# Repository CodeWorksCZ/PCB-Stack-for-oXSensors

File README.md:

# PCB Stack for oXSensors

This PCB design focuses on creating a minimalistic and efficient PCB stack for OpenXSensor project  https://github.com/mstrens/oXs_on_RP2040 , incorporating essential features such as Li-PoL  individuall cell measurement, temperature measurement using NTC, and seamless integration with external GPS modules and on-board BMP280.

This version incorporates temperature measurement using a 10K NTC thermistor, which is not originally accounted for in the [firmware](https://github.com/mstrens/oXs_on_RP2040). Therefore, a minor code addition and code compiling is necessary.

The PCB stack can be powered by standard 5V or can handle up to 12V by configuring the solder pads. This can be useful when operating high-voltage (HV) servos at 8.4V.

**Top PCB Connectors**:

- NTC 10K Thermistor
- RPM -> to CDI
- ACS758 Current Sensor and Voltage measurement

**Bottom PCB Connectors:**

- Li-Pol Cells Measurement (up to 4S) connected to on-board ADS1115
- GPS Module - e.g. BN-220
- ACS758 Current Sensor and Voltage measurement

**PCB Stack Connectors:**

Wiring and assembly instructions can be found in https://github.com/CodeWorksCZ/PCB-Stack-for-oXSensors/wiki

The initial version lacks the capability to connect additional I2C devices.

**Wiring diagram**

Precompiled firmware with the temperature calculation  based on NTC thermistor values can be [here](/oXs%20Firmware/).

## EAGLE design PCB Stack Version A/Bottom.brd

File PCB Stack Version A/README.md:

| Bottom PCB   |   Description |
|---	|---	|
|   Bottom.brd	|   Eagle Board design of Bottom PCB	|
|   Bottom.sch	|   Eagle Schematics of Bottom PCB	|
|   Bottom.pdf	|   Schematics in PDF	|
|   Top.brd	|   Eagle Board design of Top PCB	|
|   Top.sch	|   Eagle Schematics of Top PCB	|
|   Top.pdf |   Schematics in PDF	|
|   PCB Stack oXs.f3z	|   Fusion360 Files	|

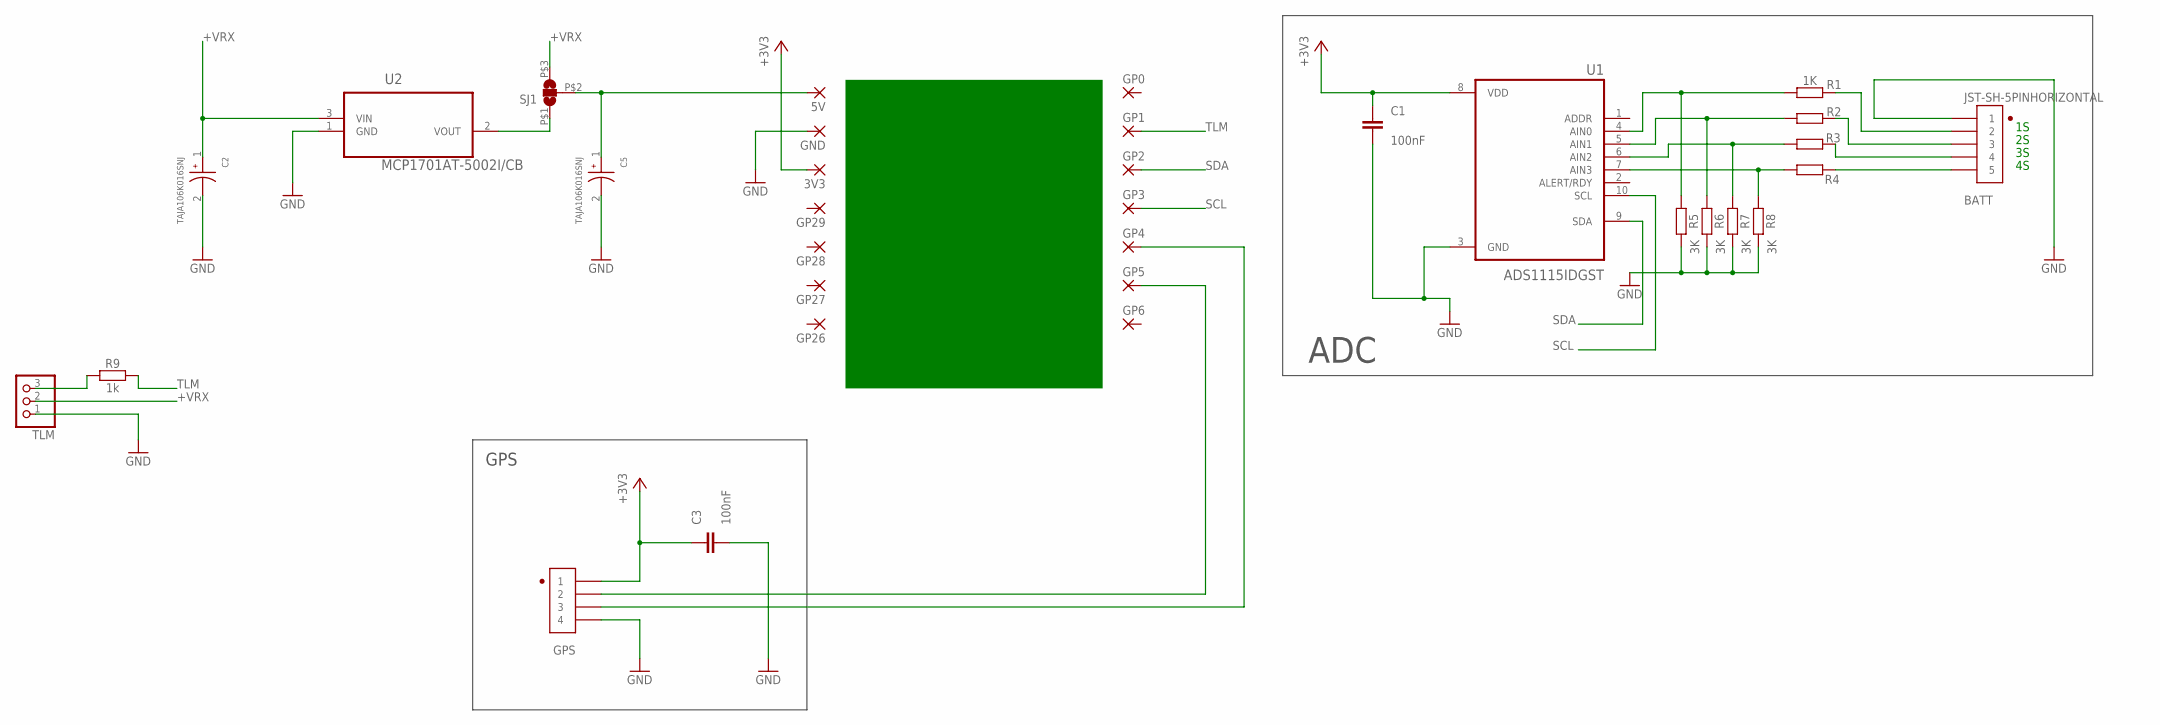
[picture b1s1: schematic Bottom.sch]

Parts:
3V3, 5V: 1,6/0,9
BATT: JST-SH-5PINHORIZONTAL; JST-SH-5PIN-1.0MM
C1, C3: 100nF; 0603
C2, C5: TAJA106K016SNJ; CAPMP3216X180N
GND: 1,6/0,9
GP0, GP1, GP2, GP3, GP4, GP5, GP6, GP26, GP27, GP28, GP29: 1,6/0,9
GPS: JST-SH-4PINJST-SH-4-HORIZONTAL; JST-SH-4PIN-1.0MM
R1: 1K; 0603
R2, R3, R4: 0603
R5, R6, R7, R8: 3K; 0603
R9: 1k; 0603
SJ1: SJ2WSJ_TINY; SJ_TINY
TLM: PINHD-1X390; 1X03-ANGLE
U1: ADS1115IDGST; SOP50P490X110-10N
U2: MCP1701AT-5002I/CB; SOT95P255X145-3N

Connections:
+3V3: 3V3.1, C1.1, C3.1, GPS.1, U1.8 (VDD)
+VRX: C2.1, SJ1.P$3 (3), TLM.2, U2.3 (VIN)
GND: BATT.1, C1.2, C2.2, C3.2, C5.2, GND.1, GPS.4, R5.2, R6.2, R7.2, R8.2, TLM.1, U1.3 (GND), U2.1 (GND)
unnamed: R1.2, R5.1, U1.4 (AIN0)
unnamed: R2.2, R6.1, U1.5 (AIN1)
unnamed: R3.2, R7.1, U1.6 (AIN2)
unnamed: R4.2, R8.1, U1.7 (AIN3)
unnamed: BATT.5, R4.1
unnamed: BATT.4, R3.1
unnamed: BATT.3, R2.1
unnamed: BATT.2, R1.1
unnamed: R9.1, TLM.3
unnamed: GP4.1, GPS.3
unnamed: GP5.1, GPS.2
unnamed: SJ1.P$1 (1), U2.2 (VOUT)
unnamed: 5V.1, C5.1, SJ1.P$2 (2)
SCL: GP3.1, U1.10 (SCL)
SDA: GP2.1, U1.9 (SDA)
TLM: GP1.1, R9.2

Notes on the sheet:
GPS
ADC

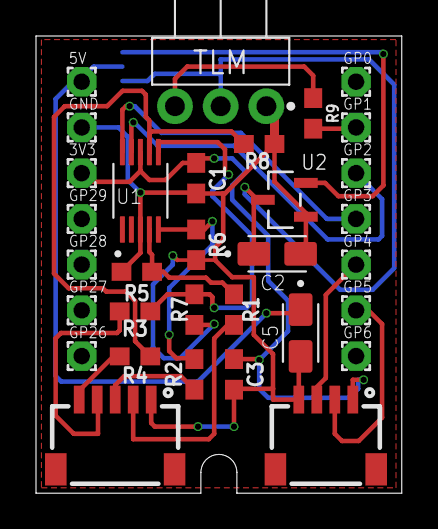
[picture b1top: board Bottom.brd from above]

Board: 2 copper layers, 20.3 x 25.4 mm, 33 parts (1 on the bottom side), 19 nets.

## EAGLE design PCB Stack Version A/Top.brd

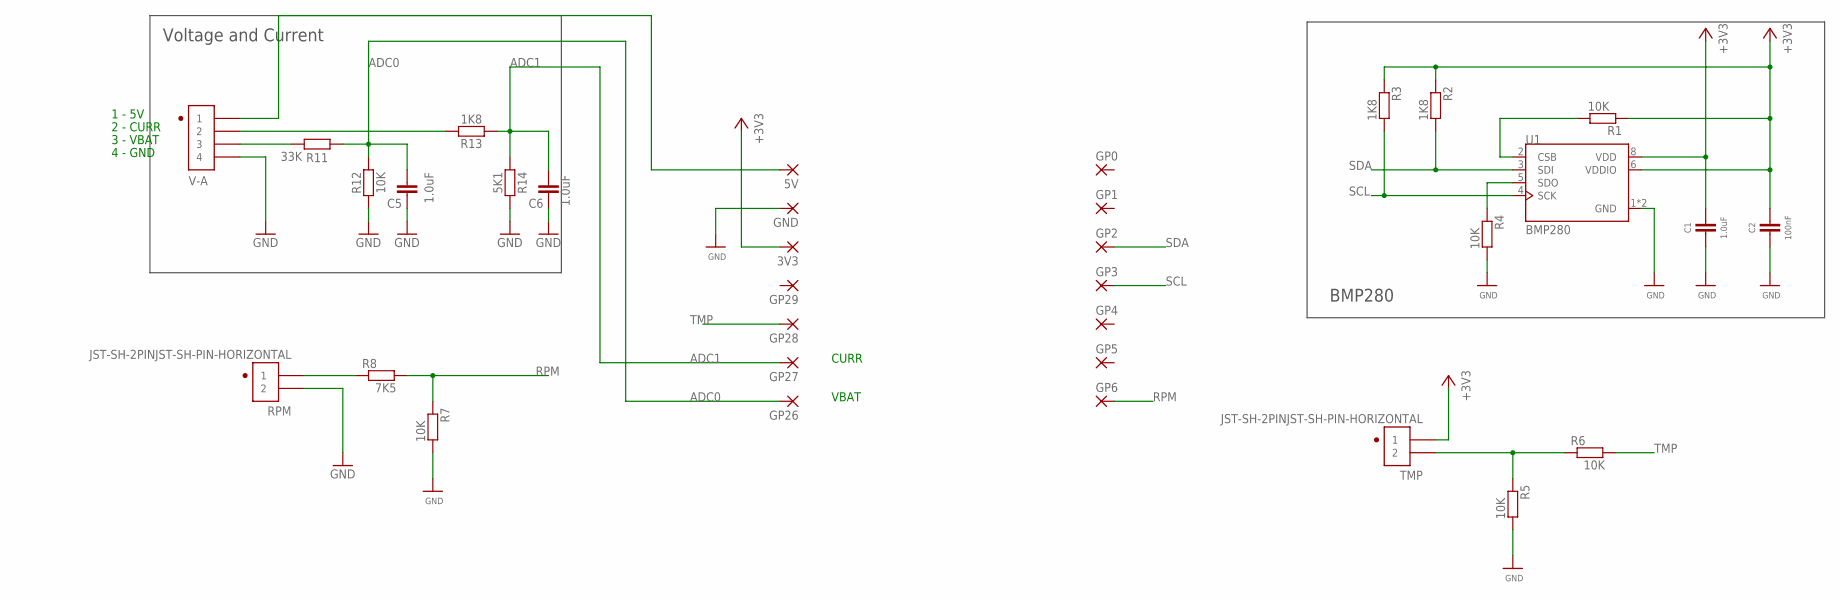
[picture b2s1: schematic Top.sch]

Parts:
3V3, 5V: 1,6/0,9
C1: 1.0uF; 0402
C2: 100nF; 0603
C5, C6: 1.0uF; 0603
GND: 1,6/0,9
GP0, GP1, GP2, GP3, GP4, GP5, GP6, GP26, GP27, GP28, GP29: 1,6/0,9
R1, R4, R5, R6, R7, R12: 10K; 0603
R2, R3, R13: 1K8; 0603
R8: 7K5; 0603
R11: 33K; 0603
R14: 5K1; 0603
RPM: JST-SH-2PINJST-SH-PIN-HORIZONTAL; JST-SH-2PIN-1.0MM
TMP: JST-SH-2PINJST-SH-PIN-HORIZONTAL; JST-SH-2PIN-1.0MM
U1: BMP280; XDCR_BMP280
V-A: JST-SH-4PINJST-SH-4-HORIZONTAL; JST-SH-4PIN-1.0MM

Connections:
+3V3: 3V3.1, C1.1, C2.1, R1.1, R2.1, R3.1, TMP.1, U1.6 (VDDIO), U1.8 (VDD)
ADC0: C5.2, GP26.1, R11.2, R12.2
ADC1: C6.2, GP27.1, R13.1, R14.1
GND: C1.2, C2.2, C5.1, C6.1, GND.1, R4.2, R5.2, R7.2, R12.1, R14.2, RPM.2, U1.1 (GND), U1.7 (GND), V-A.4
unnamed: R1.2, U1.2 (CSB)
unnamed: R4.1, U1.5 (SDO)
unnamed: R5.1, R6.1, TMP.2
unnamed: R8.1, RPM.1
unnamed: R11.1, V-A.3
unnamed: R13.2, V-A.2
unnamed: 5V.1, V-A.1
RPM: GP6.1, R7.1, R8.2
SCL: GP3.1, R3.2, U1.4 (SCK)
SDA: GP2.1, R2.2, U1.3 (SDI)
TMP: GP28.1, R6.2

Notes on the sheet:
BMP280
Voltage and Current
1 - 5V
2 - CURR
3 - VBAT
4 - GND
VBAT
CURR

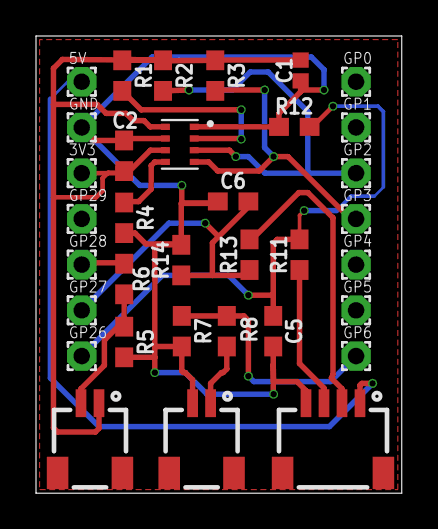
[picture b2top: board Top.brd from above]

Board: 2 copper layers, 20.3 x 25.4 mm, 34 parts (0 on the bottom side), 15 nets.

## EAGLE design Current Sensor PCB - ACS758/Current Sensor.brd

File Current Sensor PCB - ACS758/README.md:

This PCB is designed for direct connection to JST-SH connector on PCB Stack. It allows to measure current as well as voltage on connected Li-Pol battery.

**PART LIST**

|Part|Value               |Device                        |Package                  |Description           |
|----|--------------------|------------------------------|-------------------------|----------------------|
|C1  |1.0uF               |1.0UF-0603-16V-10%            |0603                     |1µF ceramic capacitors|
|C2  |1.0uF               |1.0UF-0603-16V-10%            |0603                     |1µF ceramic capacitors|
|R1  |120R                |RESISTOR0603                  |0603                     |Generic Resistor Package|
|U$1 |                    |JST-SH-4PINJST-SH-4-HORIZONTAL|JST-SH-4PIN-1.0MM        |JST-SH-4PIN-1.0MM
|U1  |ACS758LCB-100B-PFF-T|ACS758LCB-100B-PFF-T          |XDCR_ACS770KCB-150U-PFF-T|Thermally Enhanced, Fully Integrated|

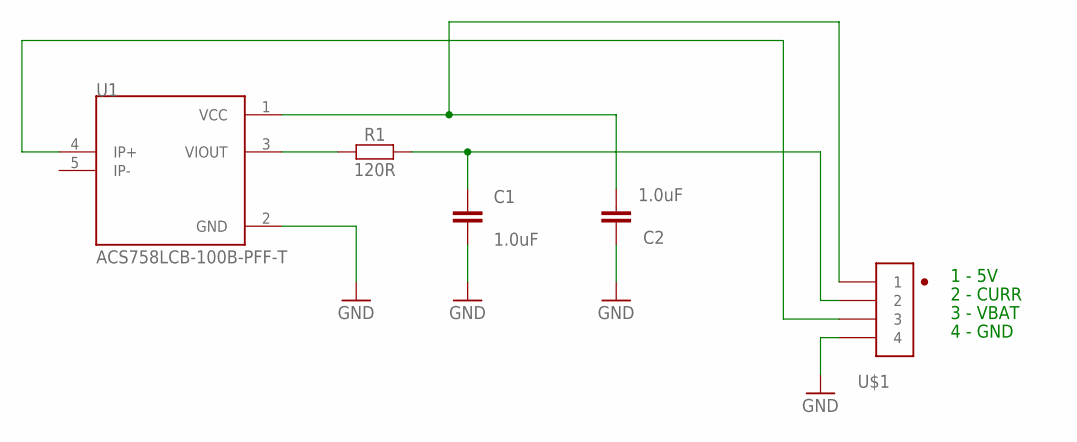
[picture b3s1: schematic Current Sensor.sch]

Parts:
C1, C2: 1.0uF; 0603
R1: 120R; 0603
U1: ACS758LCB-100B-PFF-T; XDCR_ACS770KCB-150U-PFF-T
U$1: JST-SH-4PINJST-SH-4-HORIZONTAL; JST-SH-4PIN-1.0MM

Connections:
GND: C1.2, C2.1, U1.2 (GND), U$1.4
unnamed: R1.1, U1.3 (VIOUT)
unnamed: C1.1, R1.2, U$1.2
unnamed: U1.4 (IP+), U$1.3
unnamed: C2.2, U1.1 (VCC), U$1.1

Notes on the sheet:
1 - 5V
2 - CURR
3 - VBAT
4 - GND

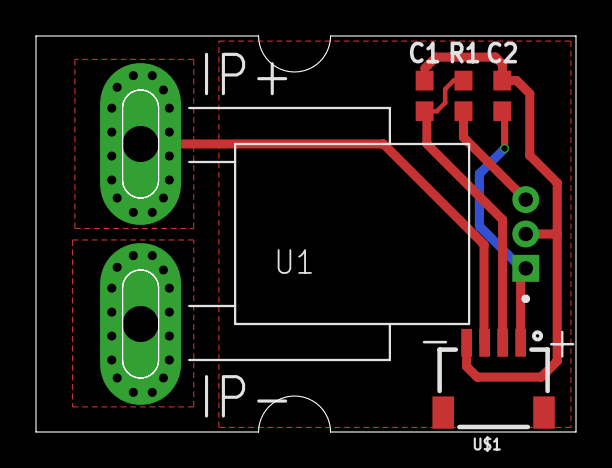
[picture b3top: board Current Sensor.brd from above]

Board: 2 copper layers, 30.0 x 22.0 mm, 5 parts (0 on the bottom side), 5 nets.

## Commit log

2023-12-08 Create images
2023-12-08 Documentation update
2023-12-11 Added Currect Sensor Folder
2023-12-11 More description added
2023-12-11 Added Enclosure
2023-12-12 mode description added
2023-12-12 PCB Added
2023-12-12 PCB Schematics and boards added
2023-12-12 edit
2023-12-12 Voltage Divider and PIN list xls added
2023-12-12 more documentation
2023-12-12 2.11.0 oXs firmware added
2023-12-12 F360 files added
2023-12-12 Typo fix
2023-12-16 Enclosure STL
2023-12-16 Enclosure Image added
